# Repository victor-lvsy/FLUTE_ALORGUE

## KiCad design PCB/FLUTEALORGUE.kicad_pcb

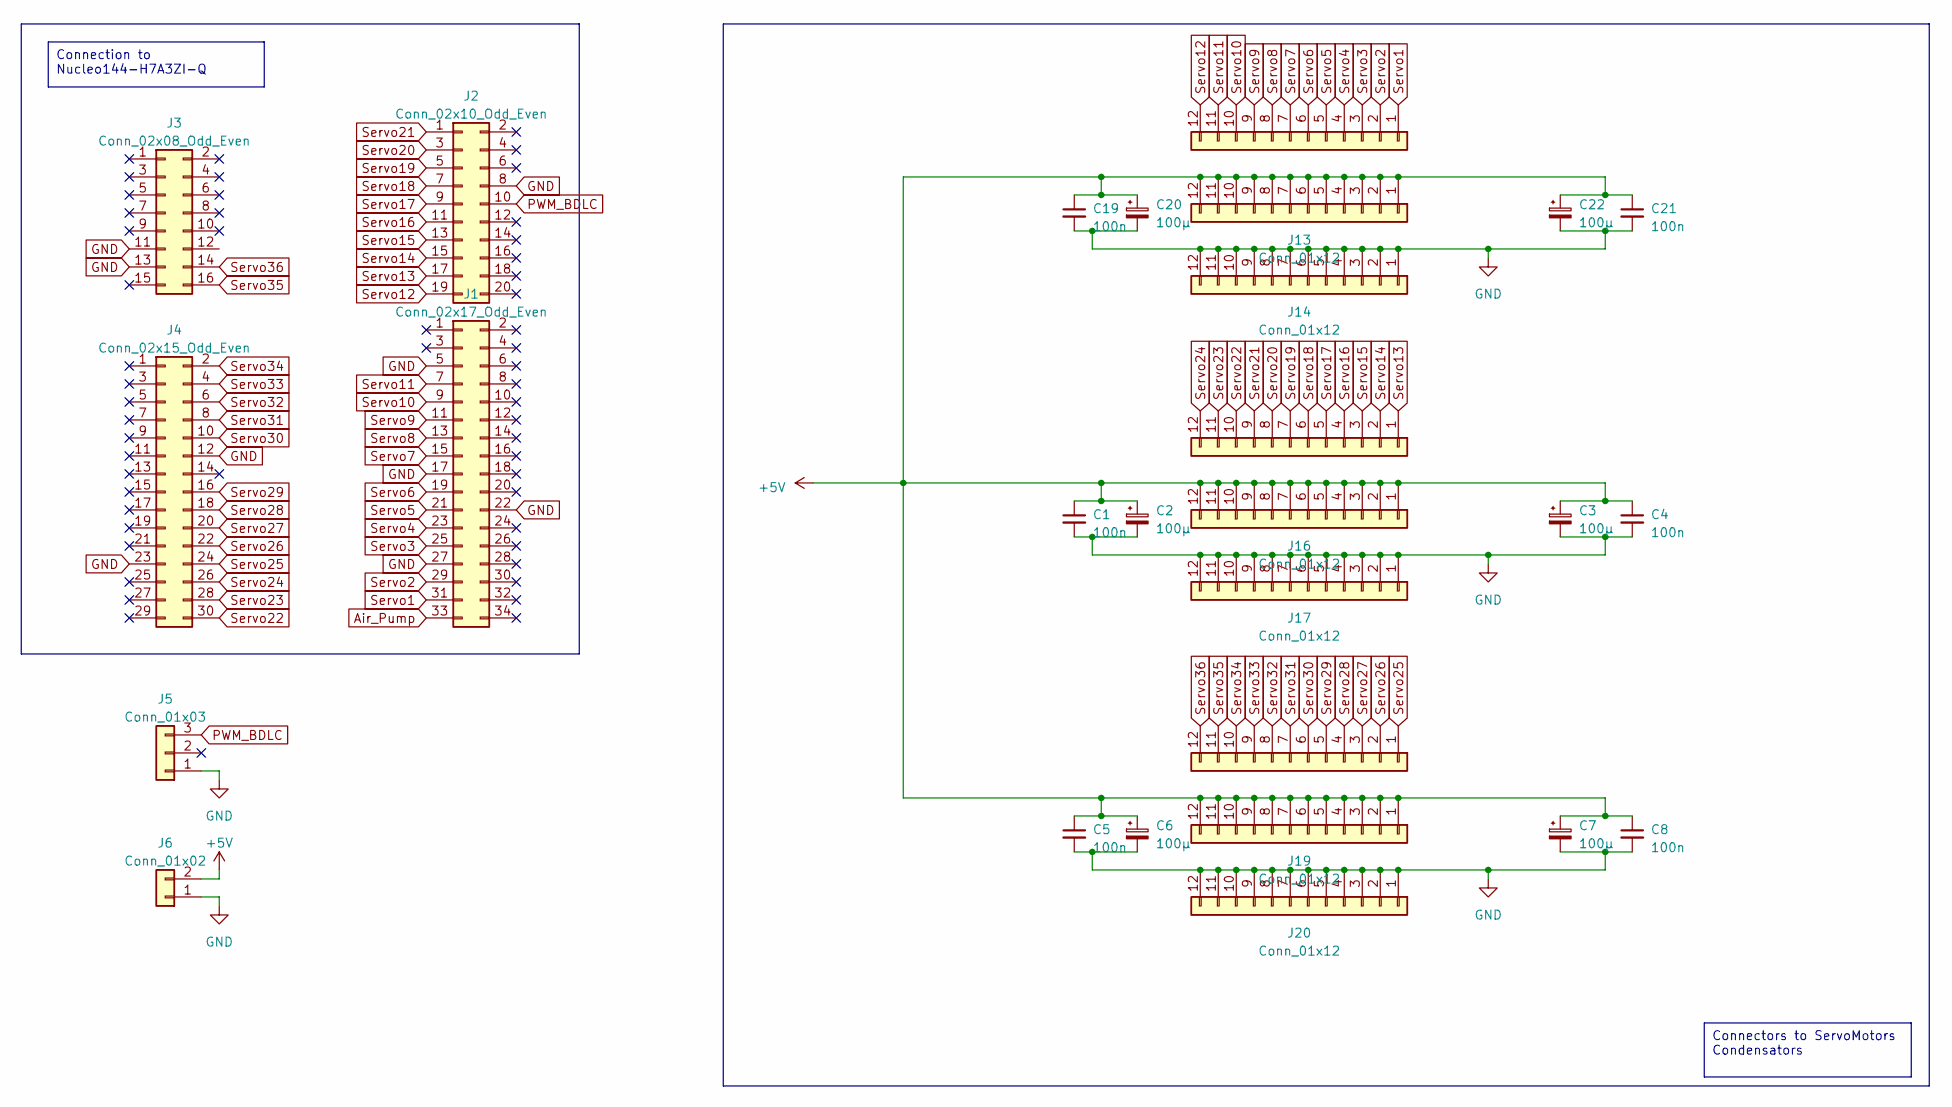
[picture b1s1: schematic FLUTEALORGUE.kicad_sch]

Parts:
C1, C4, C5, C8, C19, C21: 100n; C_0603_1608Metric_Pad1.08x0.95mm_HandSolder
C2, C3, C6, C7, C20, C22: 100µ; CP_Elec_6.3x7.7
J1: Conn_02x17_Odd_Even; PinSocket_2x17_P2.54mm_Vertical
J2: Conn_02x10_Odd_Even; PinSocket_2x10_P2.54mm_Vertical
J3: Conn_02x08_Odd_Even; PinSocket_2x08_P2.54mm_Vertical
J4: Conn_02x15_Odd_Even; PinSocket_2x15_P2.54mm_Vertical
J5: Conn_01x03; PinHeader_1x03_P2.54mm_Vertical
J6: Conn_01x02; AMASS_XT60-M_1x02_P7.20mm_Vertical
J12, J13, J14, J15, J16, J17, J18, J19, J20: Conn_01x12; PinHeader_1x12_P2.54mm_Vertical

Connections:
+5V: C1.1, C2.1, C3.1, C4.1, C5.1, C6.1, C7.1, C8.1, C19.1, C20.1, C21.1, C22.1, J6.2, J13.1, J13.2, J13.3, J13.4, J13.5, J13.6, J13.7, J13.8, J13.9, J13.10, J13.11, J13.12, J16.1, J16.2, J16.3, J16.4, J16.5, J16.6, J16.7, J16.8, J16.9, J16.10, J16.11, J16.12, J19.1, J19.2, J19.3, J19.4, J19.5, J19.6, J19.7, J19.8, J19.9, J19.10, J19.11, J19.12
Air_Pump: J1.33
GND: C1.2, C2.2, C3.2, C4.2, C5.2, C6.2, C7.2, C8.2, C19.2, C20.2, C21.2, C22.2, J1.5, J1.17, J1.22, J1.27, J2.8, J3.11, J3.13, J4.12, J4.23, J5.1, J6.1, J14.1, J14.2, J14.3, J14.4, J14.5, J14.6, J14.7, J14.8, J14.9, J14.10, J14.11, J14.12, J17.1, J17.2, J17.3, J17.4, J17.5, J17.6, J17.7, J17.8, J17.9, J17.10, J17.11, J17.12, J20.1, J20.2, J20.3, J20.4, J20.5, J20.6, J20.7, J20.8, J20.9, J20.10, J20.11, J20.12
PWM_BDLC: J2.10, J5.3
Servo1: J1.31, J12.1
Servo2: J1.29, J12.2
Servo3: J1.25, J12.3
Servo4: J1.23, J12.4
Servo5: J1.21, J12.5
Servo6: J1.19, J12.6
Servo7: J1.15, J12.7
Servo8: J1.13, J12.8
Servo9: J1.11, J12.9
Servo10: J1.9, J12.10
Servo11: J1.7, J12.11
Servo12: J2.19, J12.12
Servo13: J2.17, J15.1
Servo14: J2.15, J15.2
Servo15: J2.13, J15.3
Servo16: J2.11, J15.4
Servo17: J2.9, J15.5
Servo18: J2.7, J15.6
Servo19: J2.5, J15.7
Servo20: J2.3, J15.8
Servo21: J2.1, J15.9
Servo22: J4.30, J15.10
Servo23: J4.28, J15.11
Servo24: J4.26, J15.12
Servo25: J4.24, J18.1
Servo26: J4.22, J18.2
Servo27: J4.20, J18.3
Servo28: J4.18, J18.4
Servo29: J4.16, J18.5
Servo30: J4.10, J18.6
Servo31: J4.8, J18.7
Servo32: J4.6, J18.8
Servo33: J4.4, J18.9
Servo34: J4.2, J18.10
Servo35: J3.16, J18.11
Servo36: J3.14, J18.12

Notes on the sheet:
Connection to Nucleo144-H7A3ZI-Q
Connectors to ServoMotors Condensators

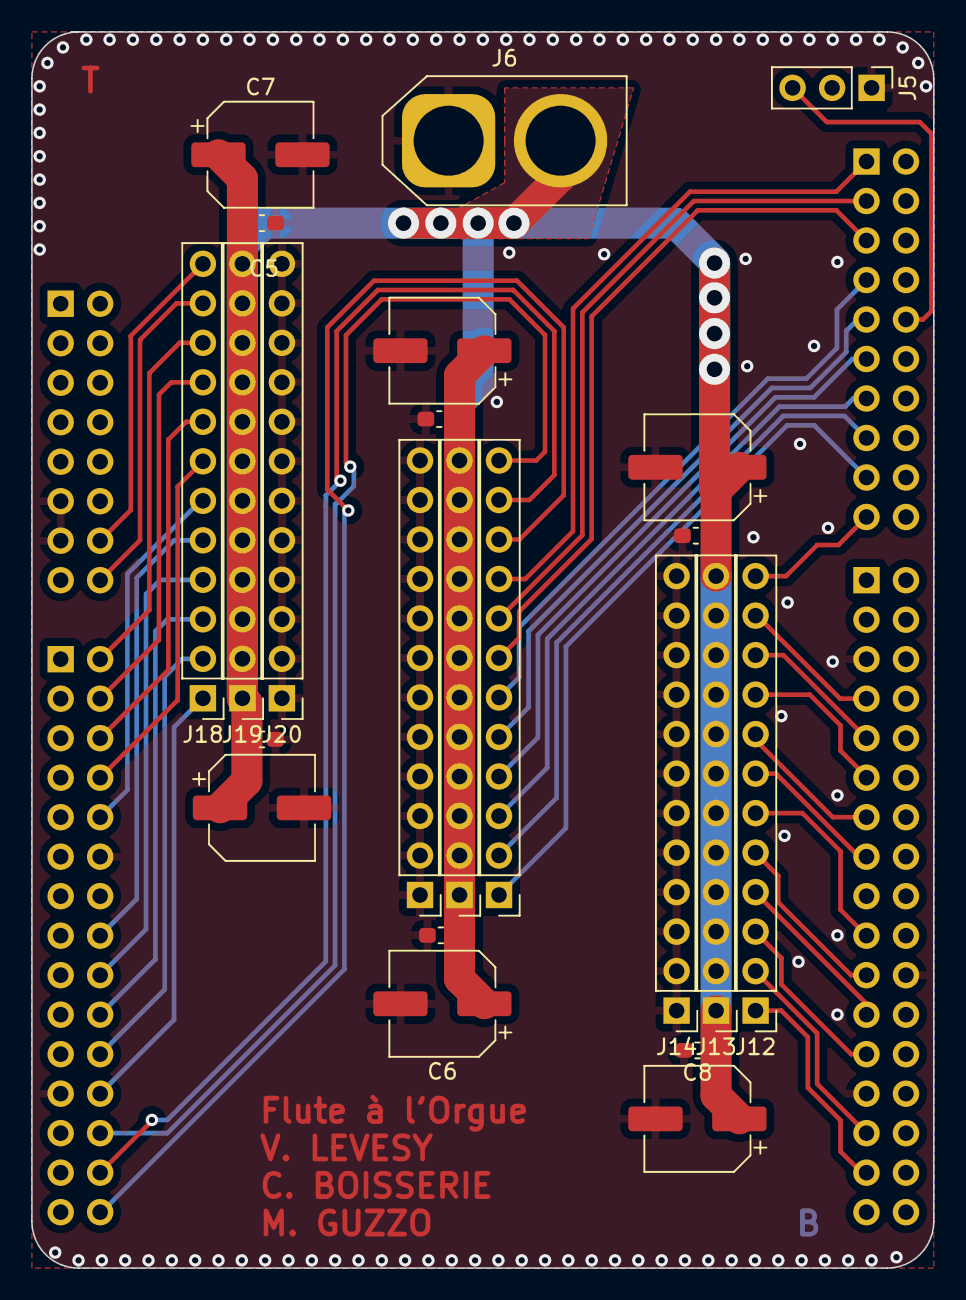
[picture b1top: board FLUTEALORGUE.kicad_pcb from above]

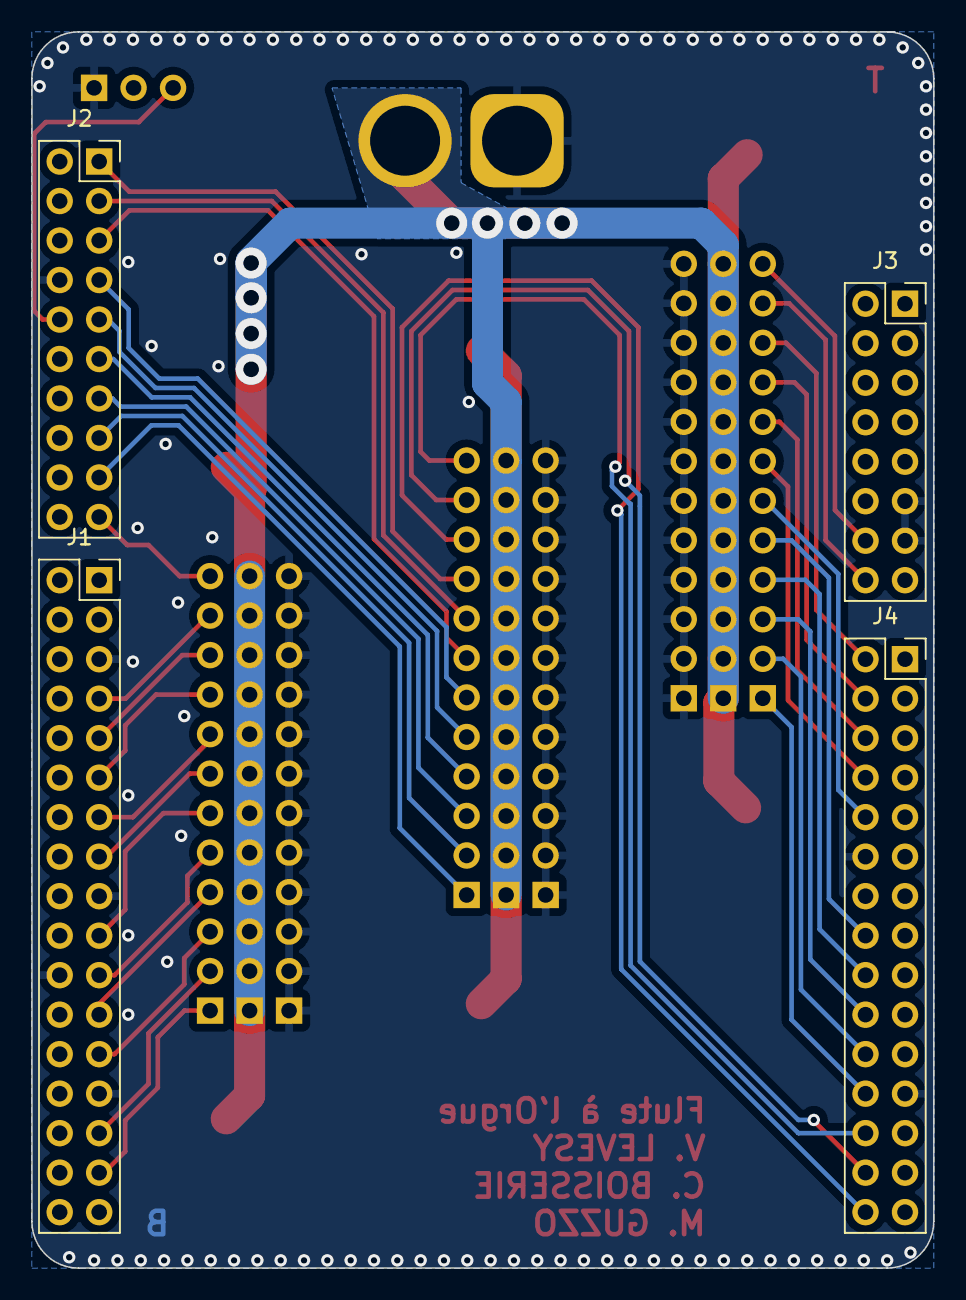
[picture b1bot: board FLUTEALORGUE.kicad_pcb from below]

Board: 2 copper layers, 58.0 x 79.5 mm, 27 parts (4 on the bottom side), 39 nets.

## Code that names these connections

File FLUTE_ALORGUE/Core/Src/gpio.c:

/* USER CODE BEGIN Header */
/**
  ******************************************************************************
  * @file    gpio.c
  * @brief   This file provides code for the configuration
  *          of all used GPIO pins.
  ******************************************************************************
  * @attention
  *
  * Copyright (c) 2023 STMicroelectronics.
  * All rights reserved.
  *
  * This software is licensed under terms that can be found in the LICENSE file
  * in the root directory of this software component.
  * If no LICENSE file comes with this software, it is provided AS-IS.
  *
  ******************************************************************************
  */
/* USER CODE END Header */

/* Includes ------------------------------------------------------------------*/
#include "gpio.h"

/* USER CODE BEGIN 0 */

/* USER CODE END 0 */

/*----------------------------------------------------------------------------*/
/* Configure GPIO                                                             */
/*----------------------------------------------------------------------------*/
/* USER CODE BEGIN 1 */

/* USER CODE END 1 */

/** Configure pins as
        * Analog
        * Input
        * Output
        * EVENT_OUT
        * EXTI
*/
void MX_GPIO_Init(void)
{

  GPIO_InitTypeDef GPIO_InitStruct = {0};

  /* GPIO Ports Clock Enable */
  __HAL_RCC_GPIOE_CLK_ENABLE();
  __HAL_RCC_GPIOC_CLK_ENABLE();
  __HAL_RCC_GPIOF_CLK_ENABLE();
  __HAL_RCC_GPIOH_CLK_ENABLE();
  __HAL_RCC_GPIOA_CLK_ENABLE();
  __HAL_RCC_GPIOB_CLK_ENABLE();
  __HAL_RCC_GPIOD_CLK_ENABLE();
  __HAL_RCC_GPIOG_CLK_ENABLE();

  /*Configure GPIO pin Output Level */
  HAL_GPIO_WritePin(GPIOE, Servo3_Pin|Servo26_Pin|Servo29_Pin|Servo28_Pin
                          |Servo27_Pin|LD2_Pin, GPIO_PIN_RESET);

  /*Configure GPIO pin Output Level */
  HAL_GPIO_WritePin(GPIOF, Servo24_Pin|Servo25_Pin|Servo23_Pin|USB_FS_PWR_EN_Pin, GPIO_PIN_RESET);

  /*Configure GPIO pin Output Level */
  HAL_GPIO_WritePin(GPIOC, Servo11_Pin|Servo10_Pin|Servo21_Pin|Servo16_Pin, GPIO_PIN_RESET);

  /*Configure GPIO pin Output Level */
  HAL_GPIO_WritePin(GPIOA, Servo2_Pin|Servo9_Pin|Servo13_Pin|Servo17_Pin, GPIO_PIN_RESET);

  /*Configure GPIO pin Output Level */
  HAL_GPIO_WritePin(GPIOB, Servo1_Pin|Servo7_Pin|Servo18_Pin|Servo19_Pin
                          |LD3_Pin|Servo20_Pin|Servo14_Pin|Servo12_Pin
                          |Servo15_Pin, GPIO_PIN_RESET);

  /*Configure GPIO pin Output Level */
  HAL_GPIO_WritePin(GPIOD, Servo22_Pin|Servo4_Pin|Servo5_Pin|Servo6_Pin
                          |Servo30_Pin|Servo31_Pin|Servo32_Pin|Servo33_Pin
                          |Servo34_Pin, GPIO_PIN_RESET);

  /*Configure GPIO pin Output Level */
  HAL_GPIO_WritePin(GPIOG, Servo8_Pin|Servo35_Pin|Servo36_Pin, GPIO_PIN_RESET);

  /*Configure GPIO pins : PEPin PEPin PEPin PEPin
                           PEPin PEPin */
  GPIO_InitStruct.Pin = Servo3_Pin|Servo26_Pin|Servo29_Pin|Servo28_Pin
                          |Servo27_Pin|LD2_Pin;
  GPIO_InitStruct.Mode = GPIO_MODE_OUTPUT_PP;
  GPIO_InitStruct.Pull = GPIO_NOPULL;
  GPIO_InitStruct.Speed = GPIO_SPEED_FREQ_LOW;
  HAL_GPIO_Init(GPIOE, &GPIO_InitStruct);

  /*Configure GPIO pin : PtPin */
  GPIO_InitStruct.Pin = B1_Pin;
  GPIO_InitStruct.Mode = GPIO_MODE_INPUT;
  GPIO_InitStruct.Pull = GPIO_NOPULL;
  HAL_GPIO_Init(B1_GPIO_Port, &GPIO_InitStruct);

  /*Configure GPIO pins : PFPin PFPin PFPin PFPin */
  GPIO_InitStruct.Pin = Servo24_Pin|Servo25_Pin|Servo23_Pin|USB_FS_PWR_EN_Pin;
  GPIO_InitStruct.Mode = GPIO_MODE_OUTPUT_PP;
  GPIO_InitStruct.Pull = GPIO_NOPULL;
  GPIO_InitStruct.Speed = GPIO_SPEED_FREQ_LOW;
  HAL_GPIO_Init(GPIOF, &GPIO_InitStruct);

  /*Configure GPIO pins : PCPin PCPin PCPin PCPin */
  GPIO_InitStruct.Pin = Servo11_Pin|Servo10_Pin|Servo21_Pin|Servo16_Pin;
  GPIO_InitStruct.Mode = GPIO_MODE_OUTPUT_PP;
  GPIO_InitStruct.Pull = GPIO_NOPULL;
  GPIO_InitStruct.Speed = GPIO_SPEED_FREQ_LOW;
  HAL_GPIO_Init(GPIOC, &GPIO_InitStruct);

  /*Configure GPIO pins : PAPin PAPin PAPin PAPin */
  GPIO_InitStruct.Pin = Servo2_Pin|Servo9_Pin|Servo13_Pin|Servo17_Pin;
  GPIO_InitStruct.Mode = GPIO_MODE_OUTPUT_PP;
  GPIO_InitStruct.Pull = GPIO_NOPULL;
  GPIO_InitStruct.Speed = GPIO_SPEED_FREQ_LOW;
  HAL_GPIO_Init(GPIOA, &GPIO_InitStruct);

  /*Configure GPIO pins : PBPin PBPin PBPin PBPin
                           PBPin PBPin PBPin PBPin
                           PBPin */
  GPIO_InitStruct.Pin = Servo1_Pin|Servo7_Pin|Servo18_Pin|Servo19_Pin
                          |LD3_Pin|Servo20_Pin|Servo14_Pin|Servo12_Pin
                          |Servo15_Pin;
  GPIO_InitStruct.Mode = GPIO_MODE_OUTPUT_PP;
  GPIO_InitStruct.Pull = GPIO_NOPULL;
  GPIO_InitStruct.Speed = GPIO_SPEED_FREQ_LOW;
  HAL_GPIO_Init(GPIOB, &GPIO_InitStruct);

  /*Configure GPIO pins : PDPin PDPin PDPin PDPin
                           PDPin PDPin PDPin PDPin
                           PDPin */
  GPIO_InitStruct.Pin = Servo22_Pin|Servo4_Pin|Servo5_Pin|Servo6_Pin
                          |Servo30_Pin|Servo31_Pin|Servo32_Pin|Servo33_Pin
                          |Servo34_Pin;
  GPIO_InitStruct.Mode = GPIO_MODE_OUTPUT_PP;
  GPIO_InitStruct.Pull = GPIO_NOPULL;
  GPIO_InitStruct.Speed = GPIO_SPEED_FREQ_LOW;
  HAL_GPIO_Init(GPIOD, &GPIO_InitStruct);

  /*Configure GPIO pins : PGPin PGPin PGPin */
  GPIO_InitStruct.Pin = Servo8_Pin|Servo35_Pin|Servo36_Pin;
  GPIO_InitStruct.Mode = GPIO_MODE_OUTPUT_PP;
  GPIO_InitStruct.Pull = GPIO_NOPULL;
  GPIO_InitStruct.Speed = GPIO_SPEED_FREQ_LOW;
  HAL_GPIO_Init(GPIOG, &GPIO_InitStruct);

  /*Configure GPIO pin : PtPin */
  GPIO_InitStruct.Pin = USB_FS_OVCR_Pin;
  GPIO_InitStruct.Mode = GPIO_MODE_IT_RISING;
  GPIO_InitStruct.Pull = GPIO_NOPULL;
  HAL_GPIO_Init(USB_FS_OVCR_GPIO_Port, &GPIO_InitStruct);

}

/* USER CODE BEGIN 2 */

/* USER CODE END 2 */

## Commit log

2023-05-11 Create test
2023-05-11 Create void
2023-05-11 Create Doc
2023-05-11 code
